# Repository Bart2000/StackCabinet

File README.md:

# StackCabinet
A modular component cabinet controlled by the touch of a finger

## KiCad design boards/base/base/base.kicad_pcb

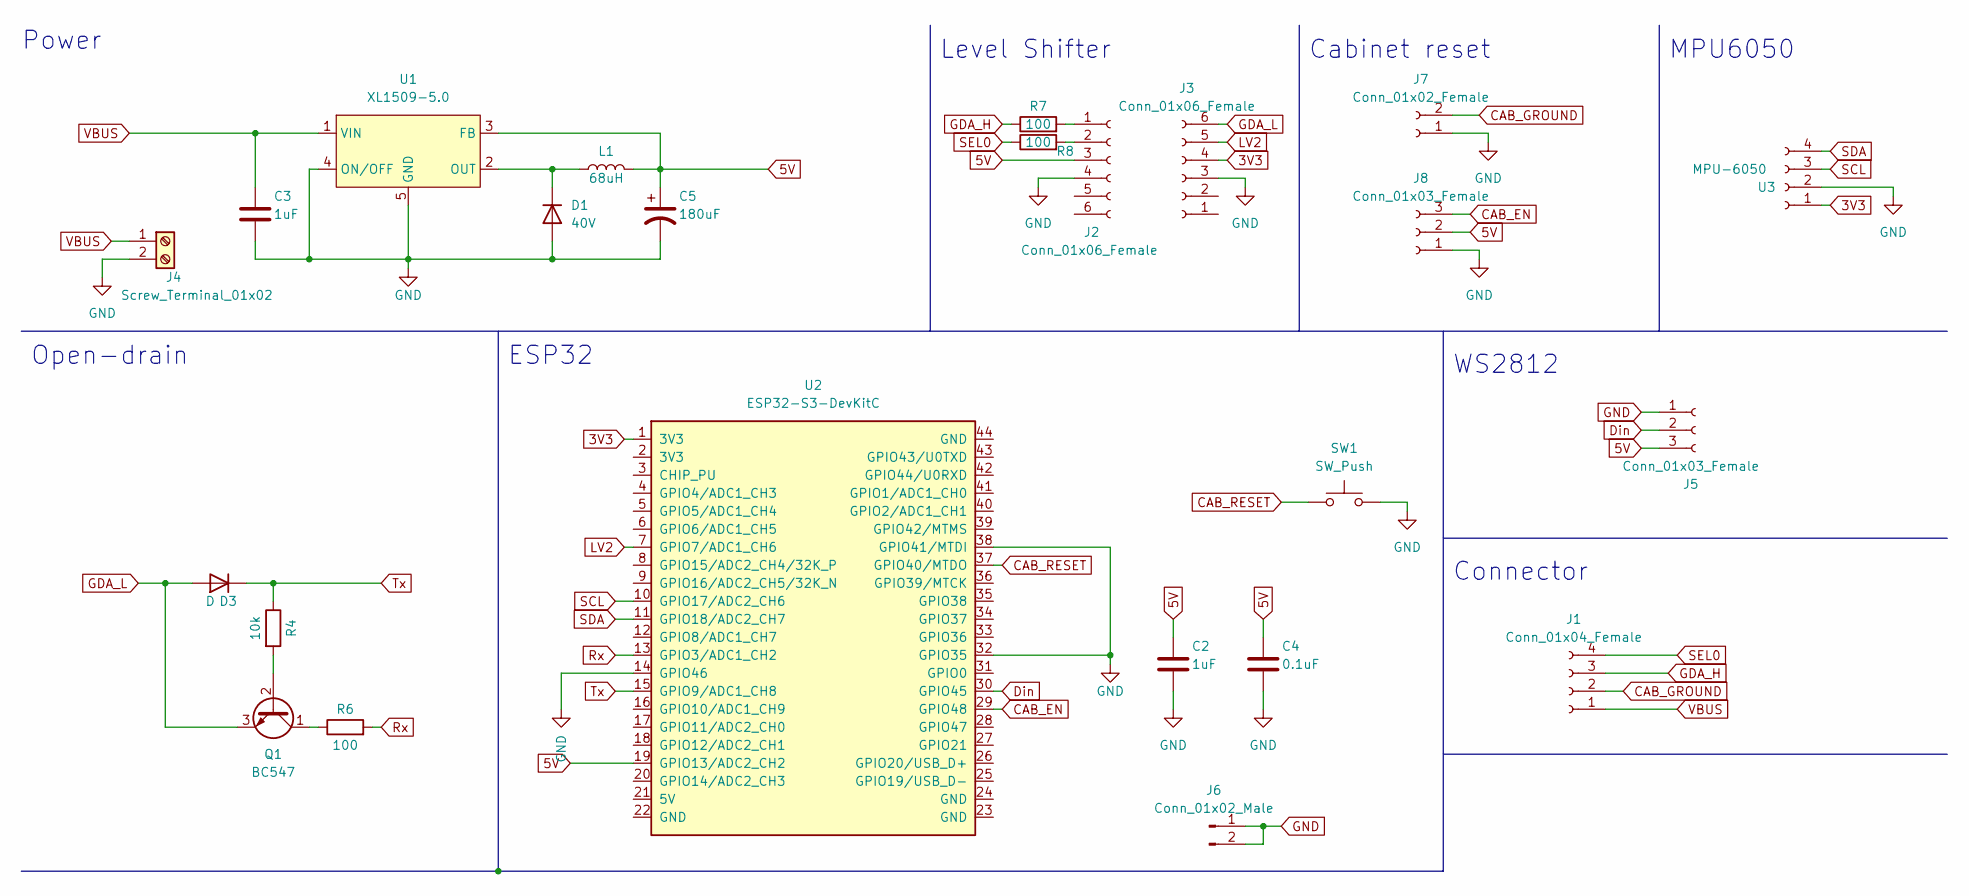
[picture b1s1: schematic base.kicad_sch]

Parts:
C2, C3: 1uF; C_0805_2012Metric; Mfr. Part# CC0805KKX7R9BB105; LCSC. Part# C91185
C4: 0.1uF; C_0805_2012Metric; Mfr. Part# C0805B104K500NT; LCSC. Part# C476766
C5: 180uF; CP_Radial_D8.0mm_P3.50mm; Mfr. Part# LKMD0901V181MF; LCSC. Part# C442870
D1: 40V; D_SOD-123; Mfr. Part# DSK34; LCSC. Part# C3015221
D3: D; R_Box_L8.4mm_W2.5mm_P5.08mm
J1: Conn_01x04_Female; PinHeader_1x04_P2.54mm_Vertical
J2, J3: Conn_01x06_Female; PinHeader_1x06_P2.54mm_Vertical
J4: Screw_Terminal_01x02; Altech_AK300_1x02_P5.00mm_45-Degree
J5, J8: Conn_01x03_Female; PinHeader_1x03_P2.54mm_Vertical
J6: Conn_01x02_Male; TerminalBlock_Altech_AK300-2_P5.00mm
J7: Conn_01x02_Female; Altech_AK300_1x02_P5.00mm_45-Degree
L1: 68uH; L_6.3x6.3_H3; Mfr. Part# CYA0650-68UH; LCSC. Part# C5189964
Q1: BC547; TO-92_Inline
R4: 10k; R_Axial_DIN0207_L6.3mm_D2.5mm_P5.08mm_Vertical
R6, R7, R8: 100; R_Axial_DIN0207_L6.3mm_D2.5mm_P5.08mm_Vertical
SW1: SW_Push; PinHeader_1x02_P2.54mm_Vertical
U1: XL1509-5.0; XLE1509; Mfr. Part# XL1509-5.0E1; LCSC. Part# C61063
U2: ESP32-S3-DevKitC; ESP32-DevKitC
U3: MPU-6050; PinHeader_1x04_P2.54mm_Vertical

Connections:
3V3: J3.4, U2.1 (3V3), U3.1
5V: C2.1, C4.1, C5.1, J2.3, J5.3, J8.2, L1.2, U1.3 (FB), U2.19 (GPIO13/ADC2_CH2)
CAB_EN: J8.3, U2.29 (GPIO48); also elsewhere on the board
CAB_GROUND: J1.2, J7.2
CAB_RESET: SW1.1, U2.37 (GPIO40/MTDO)
Din: J5.2, U2.30 (GPIO45)
GDA_H: J1.3, R7.1
GDA_L: D3.2 (A), J3.6, Q1.3 (E)
GND: C2.2, C3.2, C4.2, C5.2, D1.2 (A), J2.4, J3.3, J4.2, J5.1, J6.1, J6.2, J7.1, J8.1, SW1.2, U1.4 (ON/OFF), U1.5 (GND), U2.14 (GPIO46), U2.32 (GPIO35), U2.38 (GPIO41/MTDI), U3.2; also elsewhere on the board
LV2: J3.5, U2.7 (GPIO7/ADC1_CH6)
unnamed: D1.1 (K), L1.1, U1.2 (OUT)
unnamed: J2.1, R7.2
unnamed: J2.2, R8.2
unnamed: Q1.1 (C), R6.1
unnamed: Q1.2 (B), R4.2
Rx: R6.2, U2.13 (GPIO3/ADC1_CH2)
SCL: U2.10 (GPIO17/ADC2_CH6), U3.3
SDA: U2.11 (GPIO18/ADC2_CH7), U3.4
SEL0: J1.4, R8.1
Tx: D3.1 (K), R4.1, U2.15 (GPIO9/ADC1_CH8)
VBUS: C3.1, J1.1, J4.1, U1.1 (VIN)

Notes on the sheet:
ESP32
WS2812
Power
Open-drain
Level Shifter
Connector
Cabinet reset
MPU6050

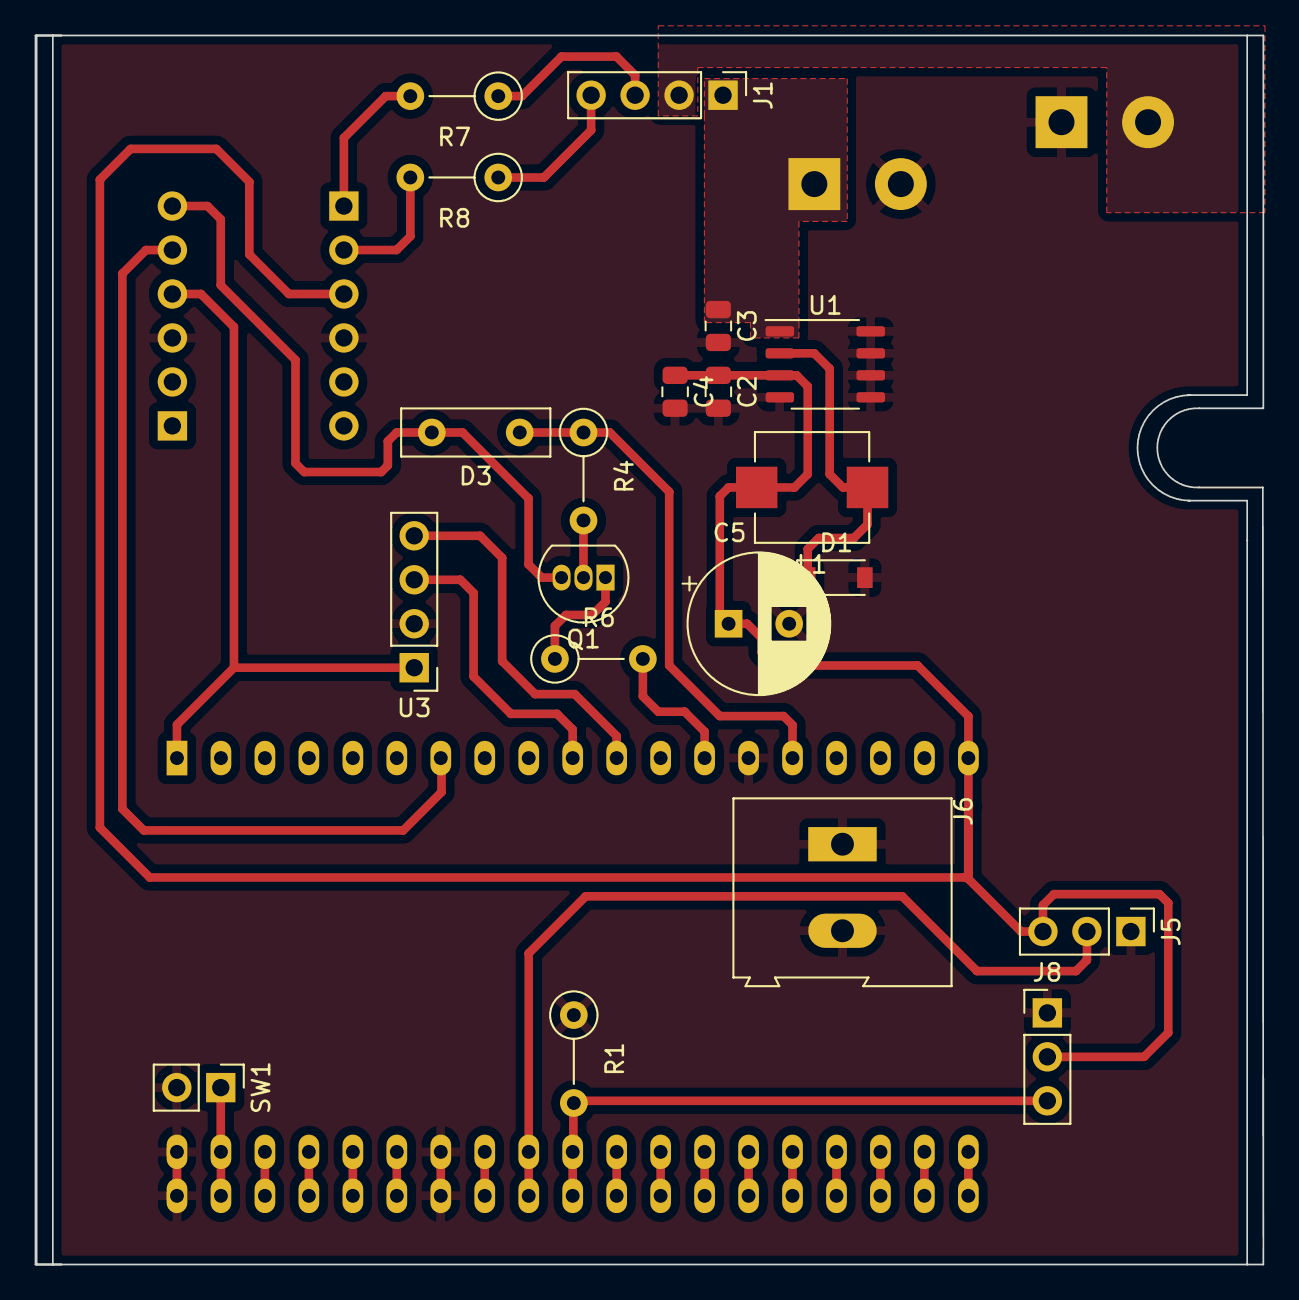
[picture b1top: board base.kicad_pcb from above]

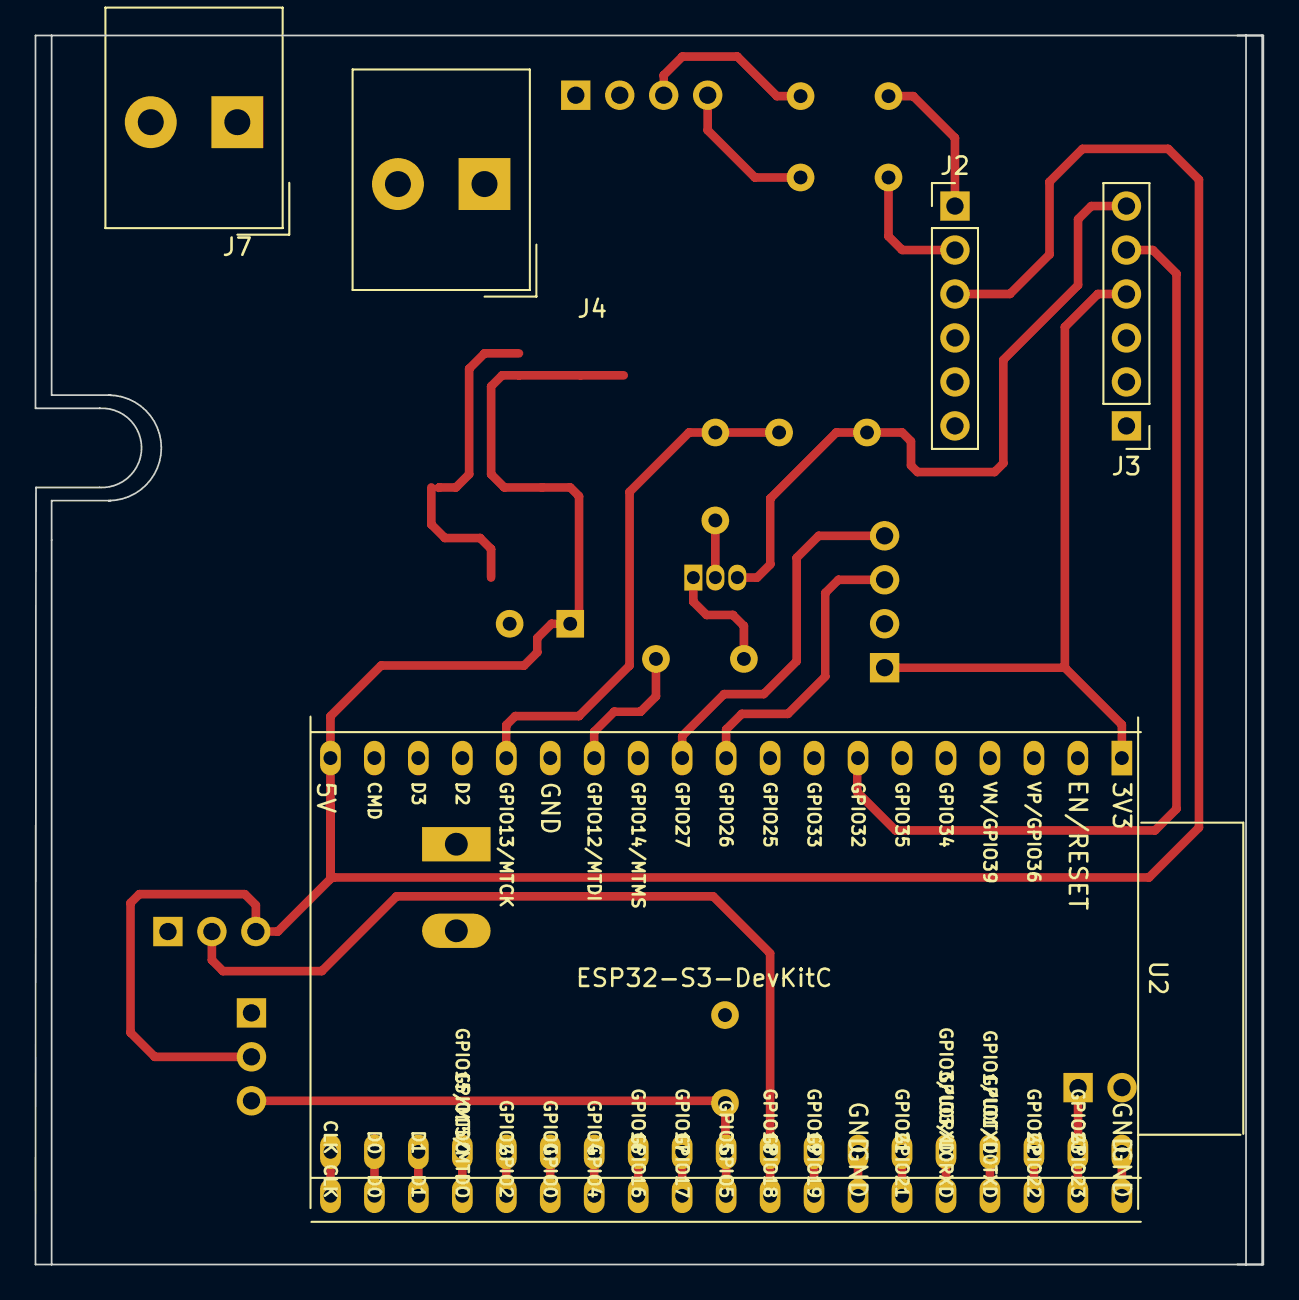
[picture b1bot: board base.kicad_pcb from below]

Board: 2 copper layers, 70.9 x 71.0 mm, 25 parts (5 on the bottom side), 21 nets.

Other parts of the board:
R1: 10k; R_Axial_DIN0207_L6.3mm_D2.5mm_P5.08mm_Vertical

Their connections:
CAB_EN: R1.2; also elsewhere on the board
GND: R1.1; also elsewhere on the board

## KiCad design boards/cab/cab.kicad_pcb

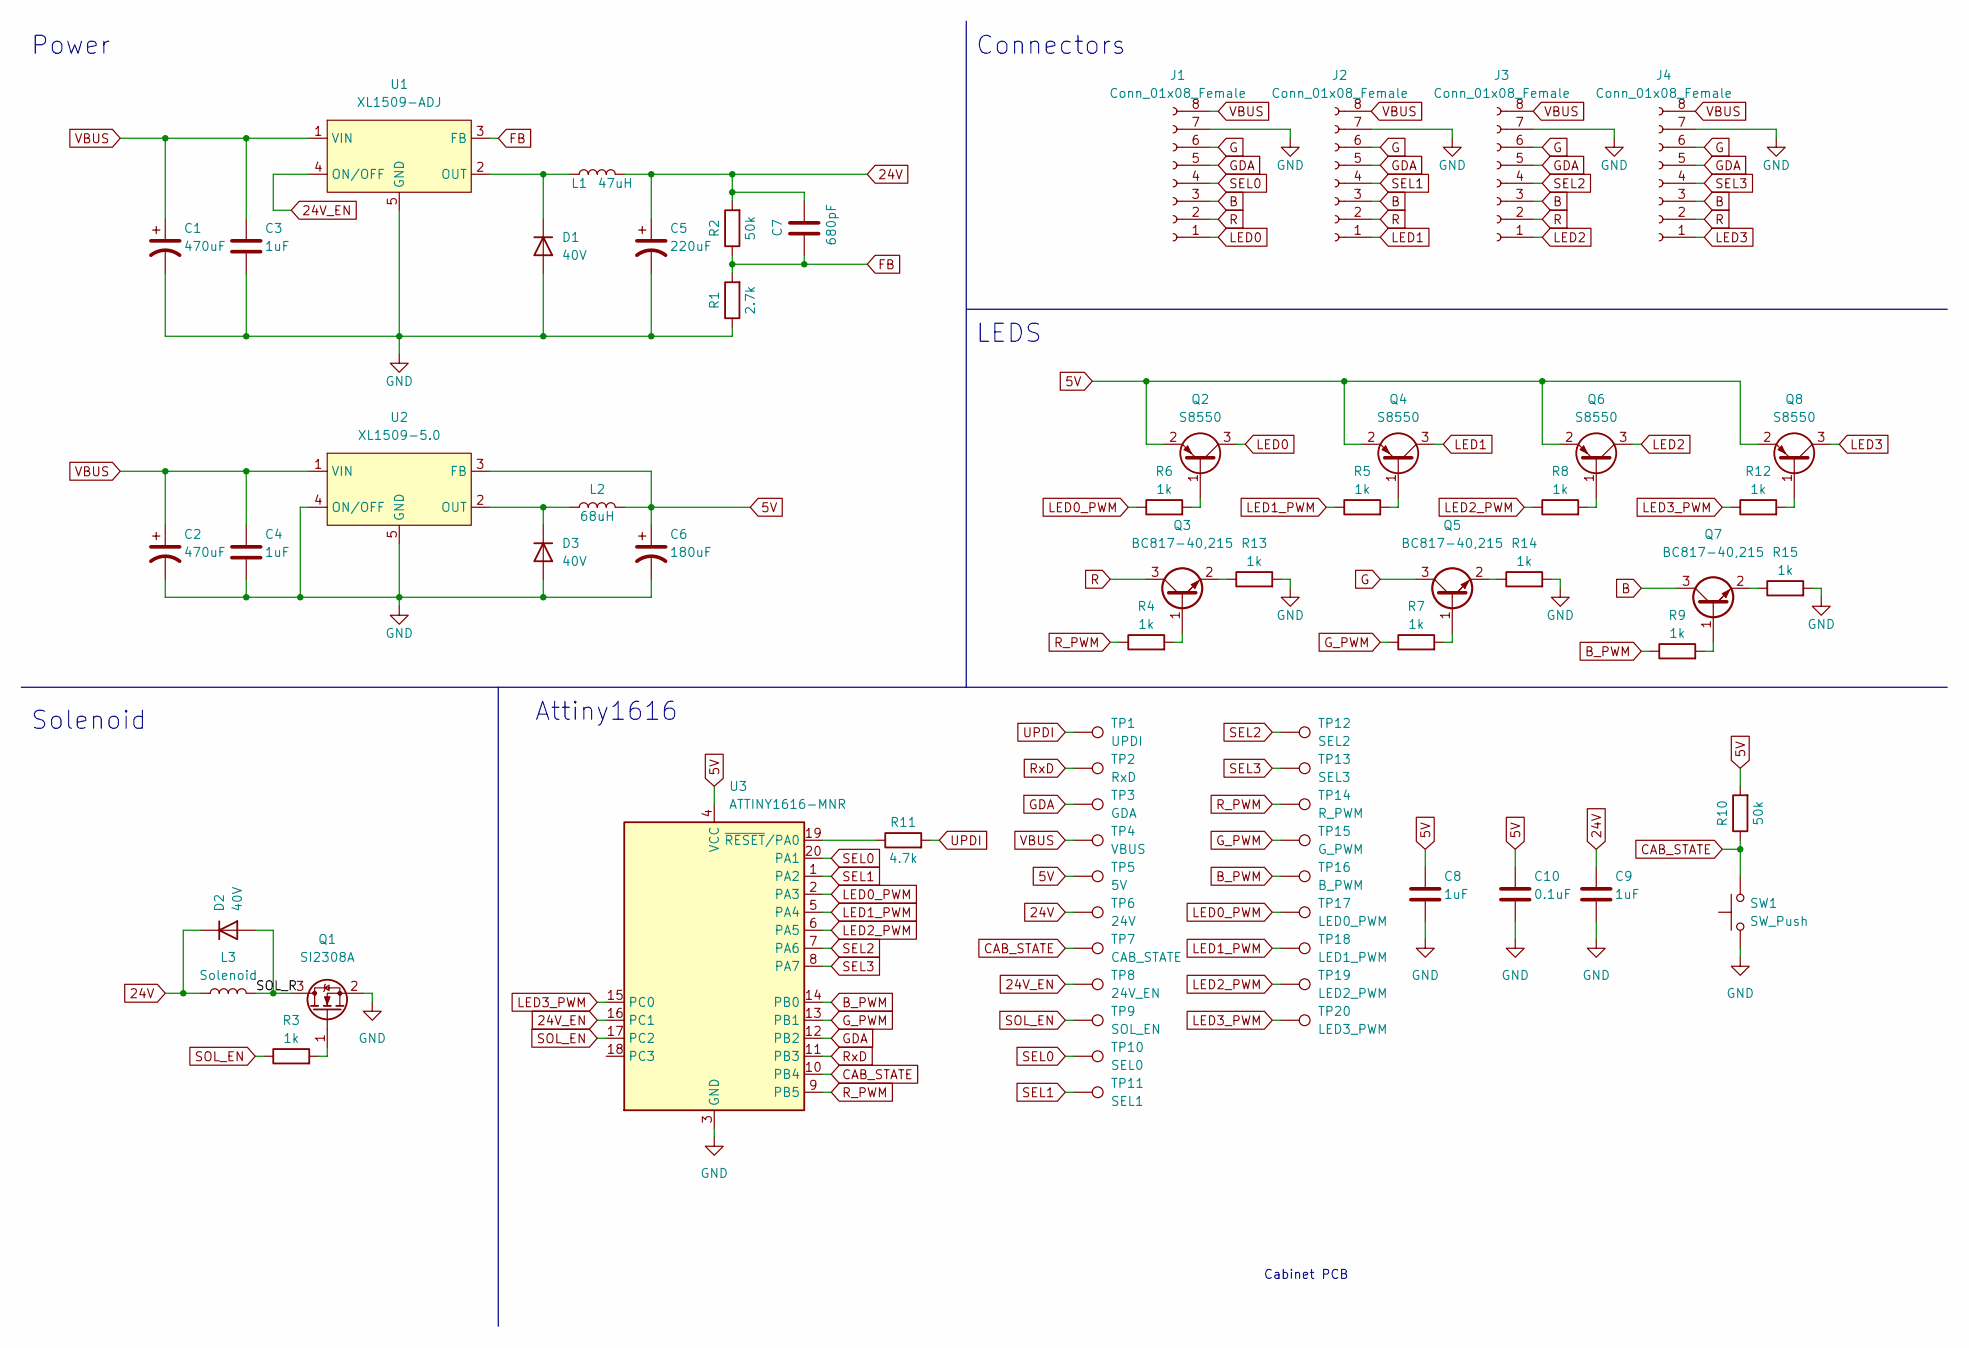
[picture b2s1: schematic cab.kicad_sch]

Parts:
C1, C2: 470uF; C_Radial_D12.5mm_H20.0mm_P5.00mm; Mfr. Part# OGPL41H471MF; LCSC. Part# C269945
C3, C4, C8, C9: 1uF; C_0805_2012Metric; Mfr. Part# CC0805KKX7R9BB105; LCSC. Part# C91185
C5: 220uF; CP_Radial_D8.0mm_P3.50mm; Mfr. Part# ECR1VBK221MLL080011; LCSC. Part# C221302
C6: 180uF; CP_Radial_D8.0mm_P3.50mm; Mfr. Part# LKMD0901V181MF; LCSC. Part# C442870
C7: 680pF; C_0805_2012Metric; Mfr. Part# 0805B681K500CT; LCSC. Part# C152864
C10: 0.1uF; C_0805_2012Metric; Mfr. Part# C0805B104K500NT; LCSC. Part# C476766
D1, D2, D3: 40V; D_SOD-123; Mfr. Part# DSK34; LCSC. Part# C3015221
J1, J2, J3, J4: Conn_01x08_Female; PinHeader_1x08_P1.27mm_Vertical; Mfr. Part# C691120; LCSC. Part# C691120
L1: 47uH; YNR1050-470M; Mfr. Part# YNR1050-470M; LCSC. Part# C5142143
L2: 68uH; L_6.3x6.3_H3; Mfr. Part# CYA0650-68UH; LCSC. Part# C5189964
L3: Solenoid; TerminalBlock_4Ucon_1x02_P3.50mm_Vertical; Mfr. Part# KF350-3.5-2P; LCSC. Part# C474892
Q1: SI2308A; SOT-23; Mfr. Part# SI2308A; LCSC. Part# C347491
Q2, Q4, Q6, Q8: S8550; SOT-23; Mfr. Part# S8550; LCSC. Part# C181159
Q3, Q5, Q7: BC817-40,215; SOT-23; Mfr. Part# BC817-40,215; LCSC. Part# C52801
R1: 2.7k; R_0805_2012Metric; Mfr. Part# ARG05FTC2701; LCSC. Part# C218493
R2, R10: 50k; R_0805_2012Metric; Mfr. Part# ARG05DTC5002; LCSC. Part# C2828840
R3, R4, R5, R6, R7, R8, R9, R12, R13, R14, R15: 1k; R_0805_2012Metric; Mfr. Part# SWR05JTEV1001; LCSC. Part# C412430
R11: 4.7k; R_0805_2012Metric; Mfr. Part# RS-05K472JT; LCSC. Part# C115310
SW1: SW_Push; PinHeader_1x02_P2.54mm_Vertical; Mfr. Part# B3F-1005; LCSC. Part# C397293
TP1: UPDI; testpad
TP2: RxD; testpad
TP3: GDA; testpad
TP4: VBUS; testpad
TP5: 5V; testpad
TP6: 24V; testpad
TP7: CAB_STATE; testpad
TP8: 24V_EN; testpad
TP9: SOL_EN; testpad
TP10: SEL0; testpad
TP11: SEL1; testpad
TP12: SEL2; testpad
TP13: SEL3; testpad
TP14: R_PWM; testpad
TP15: G_PWM; testpad
TP16: B_PWM; testpad
TP17: LED0_PWM; testpad
TP18: LED1_PWM; testpad
TP19: LED2_PWM; testpad
TP20: LED3_PWM; testpad
U1: XL1509-ADJ; XLE1509; Mfr. Part# XL1509-ADJE1; LCSC. Part# C74192
U2: XL1509-5.0; XLE1509; Mfr. Part# XL1509-5.0E1; LCSC. Part# C61063
U3: ATTINY1616-MNR; VQFN-20-1EP_3x3mm_P0.4mm_EP1.7x1.7mm; Mfr. Part# ATTINY1616-MNR; LCSC. Part# C507118

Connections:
5V: C6.1, C8.1, C10.1, L2.2, Q2.2 (E), Q4.2 (E), Q6.2 (E), Q8.2 (E), R10.2, TP5.1, U2.3 (FB), U3.4 (VCC)
24V: C5.1, C7.1, C9.1, D2.1 (K), L1.2, L3.1, R2.2, TP6.1
24V_EN: TP8.1, U1.4 (ON/OFF), U3.16 (PC1)
/SOL_R: D2.2 (A), L3.2, Q1.3 (D)
B: J1.3, J2.3, J3.3, J4.3, Q7.3 (C)
B_PWM: R9.1, TP16.1, U3.14 (PB0)
CAB_STATE: R10.1, SW1.2, TP7.1, U3.10 (PB4)
FB: C7.2, R1.2, R2.1, U1.3 (FB)
G: J1.6, J2.6, J3.6, J4.6, Q5.3 (C)
GDA: J1.5, J2.5, J3.5, J4.5, TP3.1, U3.12 (PB2)
GND: C1.2, C2.2, C3.2, C4.2, C5.2, C6.2, C8.2, C9.2, C10.2, D1.2 (A), D3.2 (A), J1.7, J2.7, J3.7, J4.7, Q1.2 (S), R1.1, R13.2, R14.2, R15.2, SW1.1, U1.5 (GND), U2.4 (ON/OFF), U2.5 (GND), U3.3 (GND), U3.21 (GND)
G_PWM: R7.1, TP15.1, U3.13 (PB1)
LED0: J1.1, Q2.3 (C)
LED0_PWM: R6.1, TP17.1, U3.2 (PA3)
LED1: J2.1, Q4.3 (C)
LED1_PWM: R5.1, TP18.1, U3.5 (PA4)
LED2: J3.1, Q6.3 (C)
LED2_PWM: R8.1, TP19.1, U3.6 (PA5)
LED3: J4.1, Q8.3 (C)
LED3_PWM: R12.1, TP20.1, U3.15 (PC0)
unnamed: D1.1 (K), L1.1, U1.2 (OUT)
unnamed: D3.1 (K), L2.1, U2.2 (OUT)
unnamed: Q1.1 (G), R3.2
unnamed: Q2.1 (B), R6.2
unnamed: Q3.1 (B), R4.2
unnamed: Q3.2 (E), R13.1
unnamed: Q4.1 (B), R5.2
unnamed: Q5.1 (B), R7.2
unnamed: Q5.2 (E), R14.1
unnamed: Q6.1 (B), R8.2
unnamed: Q7.1 (B), R9.2
unnamed: Q7.2 (E), R15.1
unnamed: Q8.1 (B), R12.2
unnamed: R11.1, U3.19 (~RESET/PA0)
R: J1.2, J2.2, J3.2, J4.2, Q3.3 (C)
R_PWM: R4.1, TP14.1, U3.9 (PB5)
RxD: TP2.1, U3.11 (PB3)
SEL0: J1.4, TP10.1, U3.20 (PA1)
SEL1: J2.4, TP11.1, U3.1 (PA2)
SEL2: J3.4, TP12.1, U3.7 (PA6)
SEL3: J4.4, TP13.1, U3.8 (PA7)
SOL_EN: R3.1, TP9.1, U3.17 (PC2)
UPDI: R11.2, TP1.1
VBUS: C1.1, C2.1, C3.1, C4.1, J1.8, J2.8, J3.8, J4.8, TP4.1, U1.1 (VIN), U2.1 (VIN)

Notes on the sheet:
LEDS
Connectors
Cabinet PCB
Power
Solenoid
Attiny1616

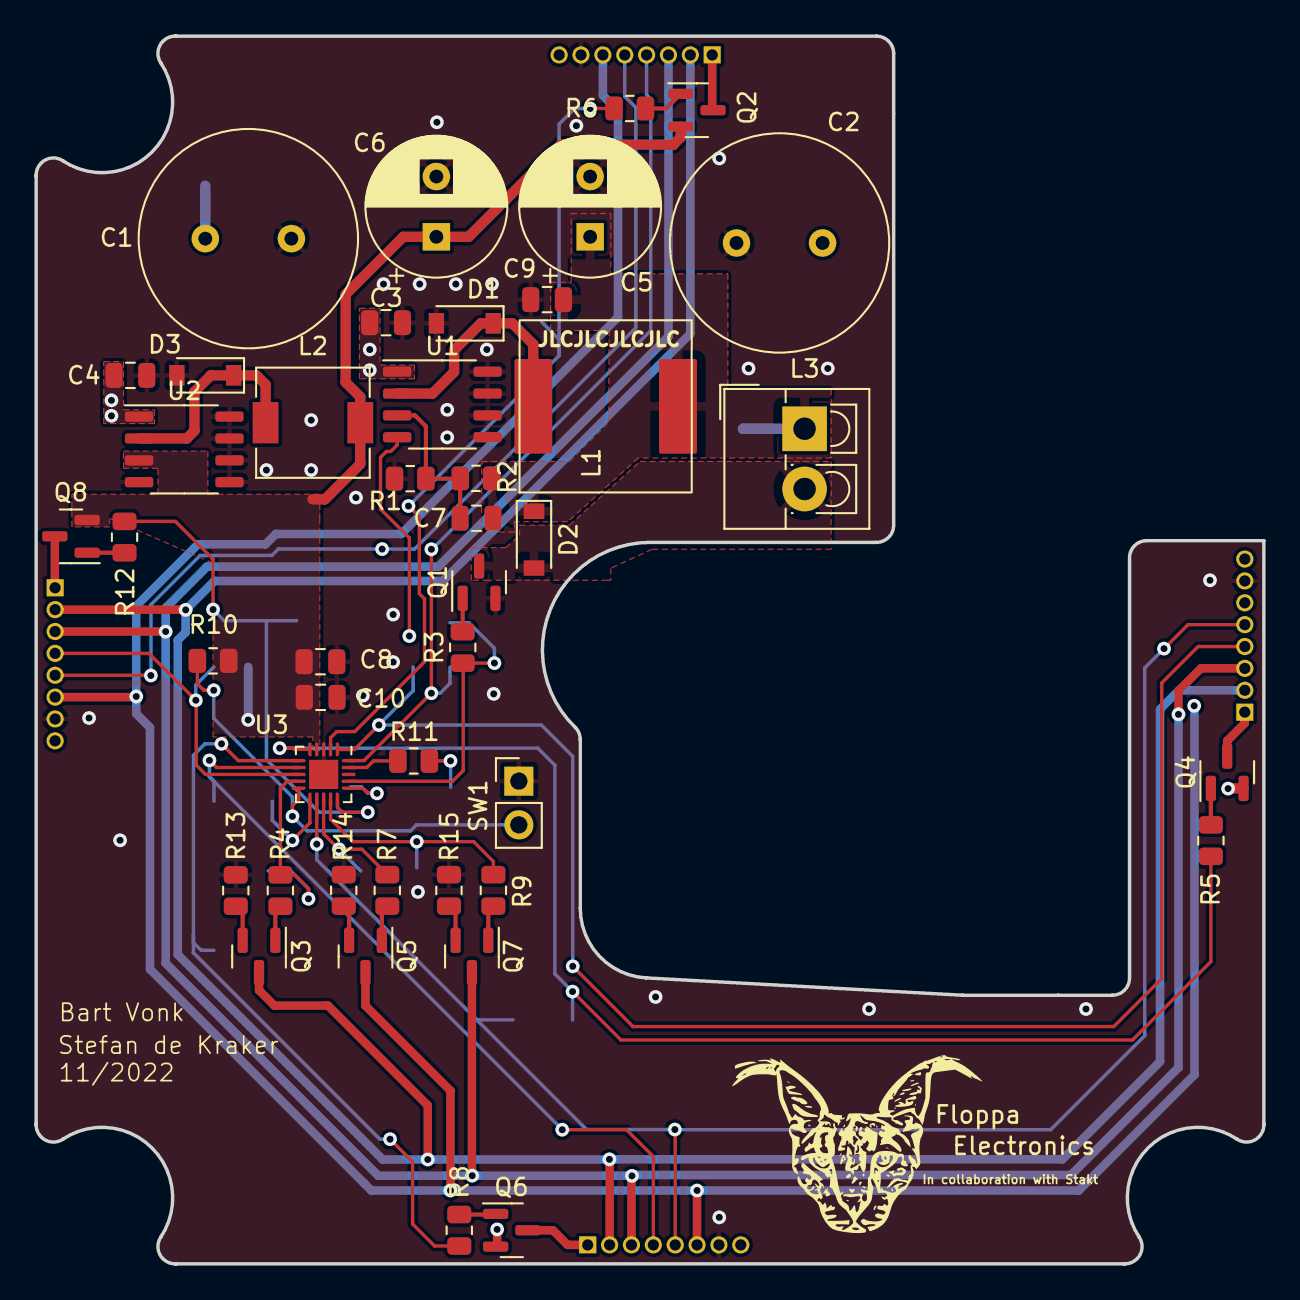
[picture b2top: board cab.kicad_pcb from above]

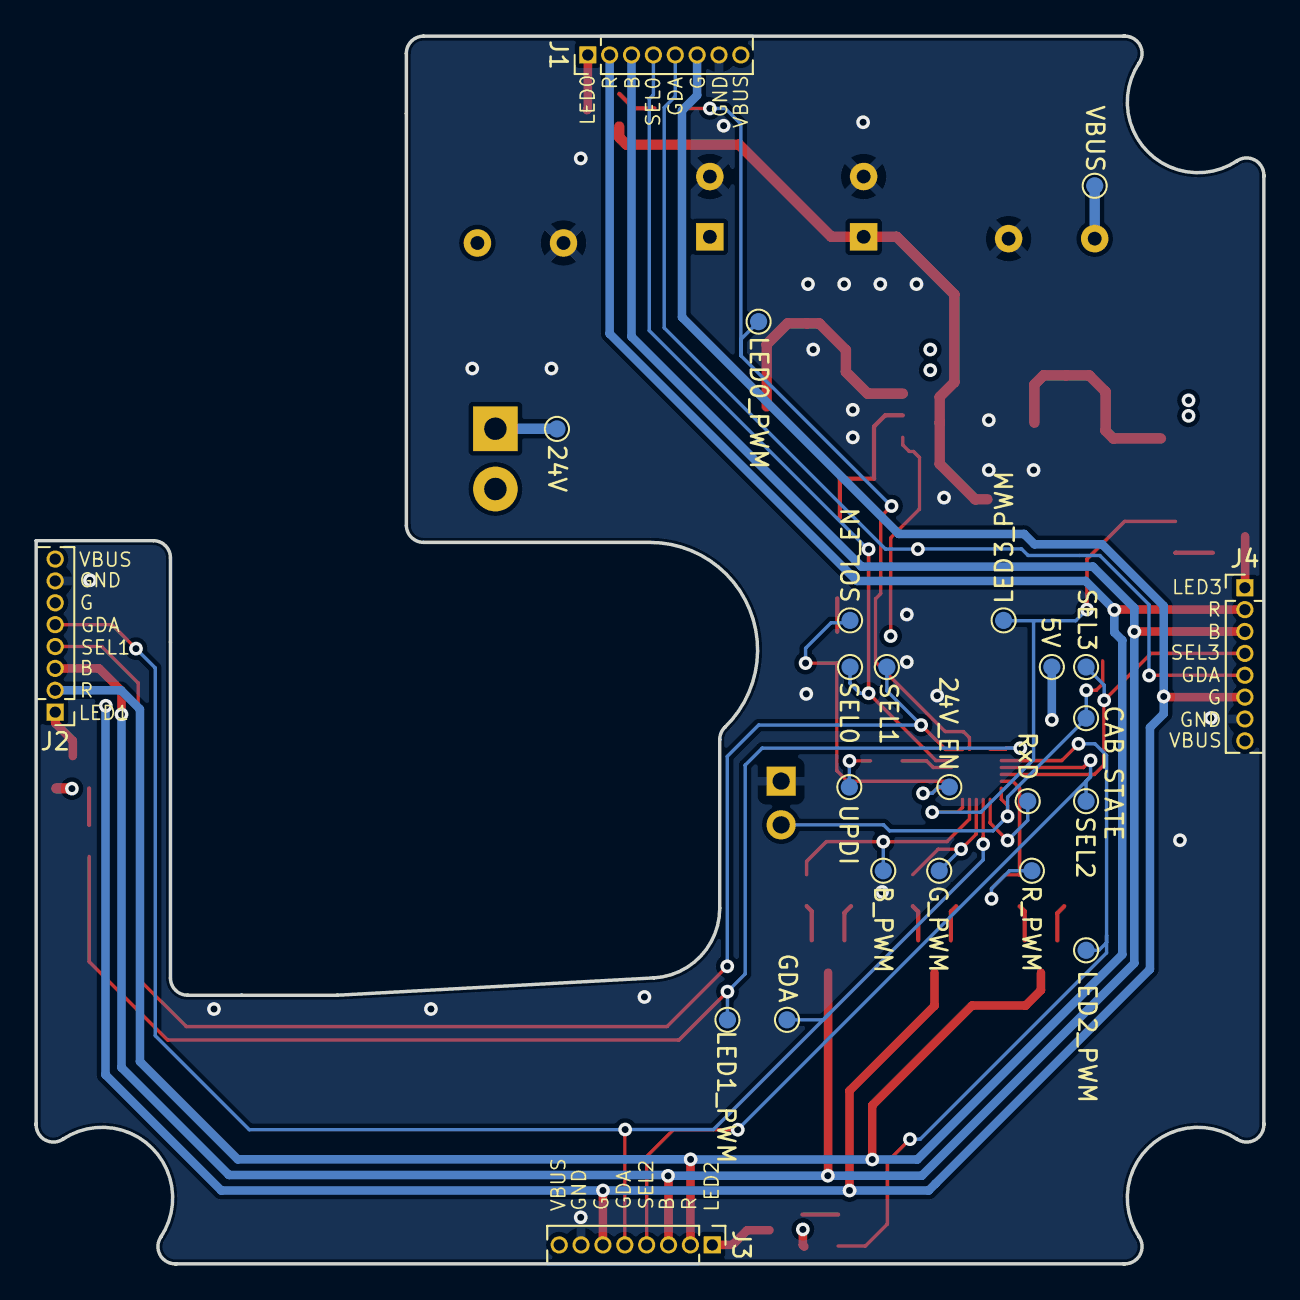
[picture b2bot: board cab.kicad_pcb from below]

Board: 4 copper layers, 71.3 x 71.3 mm, 67 parts (4 on the bottom side), 44 nets.

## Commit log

2022-09-27 Added SCCP vizualization
2022-09-27 Initialized PlatformIO project
2022-09-27 Added configuration for pyupdi
2022-10-02 Added blinky
2022-10-03 Added print example
2022-10-03 Added SCCP class
2022-10-03 Added SCCP struct
2022-10-03 Added encode and decode methods
2022-10-06 Added dynamic method handling
2022-10-09 Added gate check
2022-10-09 Finished ICAB handler
2022-10-09 Added agat implementation
2022-10-09 Implemented DGAT command
2022-10-09 Added rx disable
2022-10-09 Implemented receive poll
2022-10-09 ESP32 test
2022-10-10 Added RXC receive interrupt and baudrate error correction
2022-10-10 Moved SCCP library
2022-10-10 Added setup function
2022-10-10 Added comments
2022-10-10 Added simple esp32 sketch
2022-10-13 Initialized KiCad schematic
2022-10-14 Added power schematic
2022-10-14 Init StackCabinet Companion App
2022-10-17 Removed hierarchy and added Connectors, Leds
2022-10-24 Updated schematic
2022-10-28 Created PCB
2022-10-29 Finished schematic
2022-10-29 Reworked board outline
2022-10-29 Fixed mosfet footprint
2022-10-29 Placed Power, Attiny and LED power
2022-11-13 Routing & planes
2022-11-13 Tuned polygons
2022-11-14 Convert to 4 layer
2022-11-14 Setup BluetoothRepository, viewModel, Permissions and UI
2022-11-15 Added vias
2022-11-16 Setup permissions, search for bluetooth devices, and pair to selected devices.
2022-11-17 Added connect and connected Threads, these Threads are used to, 1. setup a connection with a Bluetooth devices, and 2. to open a Input and Output stream to send and receive data
2022-11-17 Cleanup of code and added comments
2022-11-17 Simple setup of the Grid compose view and ViewModel, implements the new Threads in the repository to send and receive data from a bluetooth device
2022-11-19 Started with PWM
2022-11-19 Update file tree
2022-11-20 Added 8 PWM channels
2022-11-20 Added LED resistors, changed routing
2022-11-20 Created ESP32 SCCP wrapper and started identification
2022-11-21 Added silklayer text and generated gerber
2022-11-22 esp32 identification
2022-11-22 Added receive loop
2022-11-23 Made SCCP wrapper for esp32
2022-11-25 Added vector
2022-11-27 Implemented functioning SCCP identification
2022-11-28 removed comments
2022-11-28 Cleaned code
2022-11-30 Identification improved
2022-12-01 Finished identification, added comments
2022-12-04 Identification switched to port A
2022-12-05 Working Grid, able to calculate the X and Y coordinates for each Cabinet
2022-12-05 Added double Click to Cabinet, and keep the UI state
2022-12-12 Fixed gate activation
2022-12-13 Started BasePCB
2022-12-19 Finished BasePCB
2022-12-23 Added cab_reset and base LED
2022-12-23 Added led_strip
2022-12-23 Final version of BasePCB
2023-01-10 Added diode on base
2023-01-10 Temporary
2023-01-11 Made RGB leds for 3 strip
2023-01-11 Added write/read eeprom
2023-01-12 Added reset button detect
2023-01-13 Its not working
2023-01-13 Tidied Base PCB
2023-01-14 Backups
2023-01-15 Fixed issues when user does not allow permissions
2023-01-15 Complete changed UI setup, single ViewModel for 2 screens
2023-01-16 need other branch
2023-01-16 beunweek
2023-01-16 fixed for PR #23
2023-01-17 Fixed EEPROM
2023-01-17 added neede libs
2023-01-17 Added SPROD SCCP command
2023-01-17 Added product id to graph
2023-01-17 Added the led_strip lib to the cmake file
2023-01-17 Setup Bluetooth class
2023-01-17 clean upp sdkconfig
2023-01-18 Wtf is this
2023-01-18 tmp commit
2023-01-19 Revert issues with the file
2023-01-19 Fixed base
2023-01-19 hamburga
2023-01-19 Base V2
2023-01-20 Changed routing
2023-01-20 zippie
2023-01-23 fixed it bro
2023-01-23 added 3D models, and roll back to ESP-IDF 4.4.2
2023-01-23 fixed flipped layout Cabinets
2023-01-23 update config
2023-01-23 cleanup back-ups
2023-01-23 renamed folder name
2023-01-25 Update gitignore
2023-01-25 Cleanup
2023-01-27 Fixed bluetooth, and added LED status
2023-01-27 Fixed design
2023-01-27 Changed way of sending / receiving command, and added a clickable option on the CabinetCompose
